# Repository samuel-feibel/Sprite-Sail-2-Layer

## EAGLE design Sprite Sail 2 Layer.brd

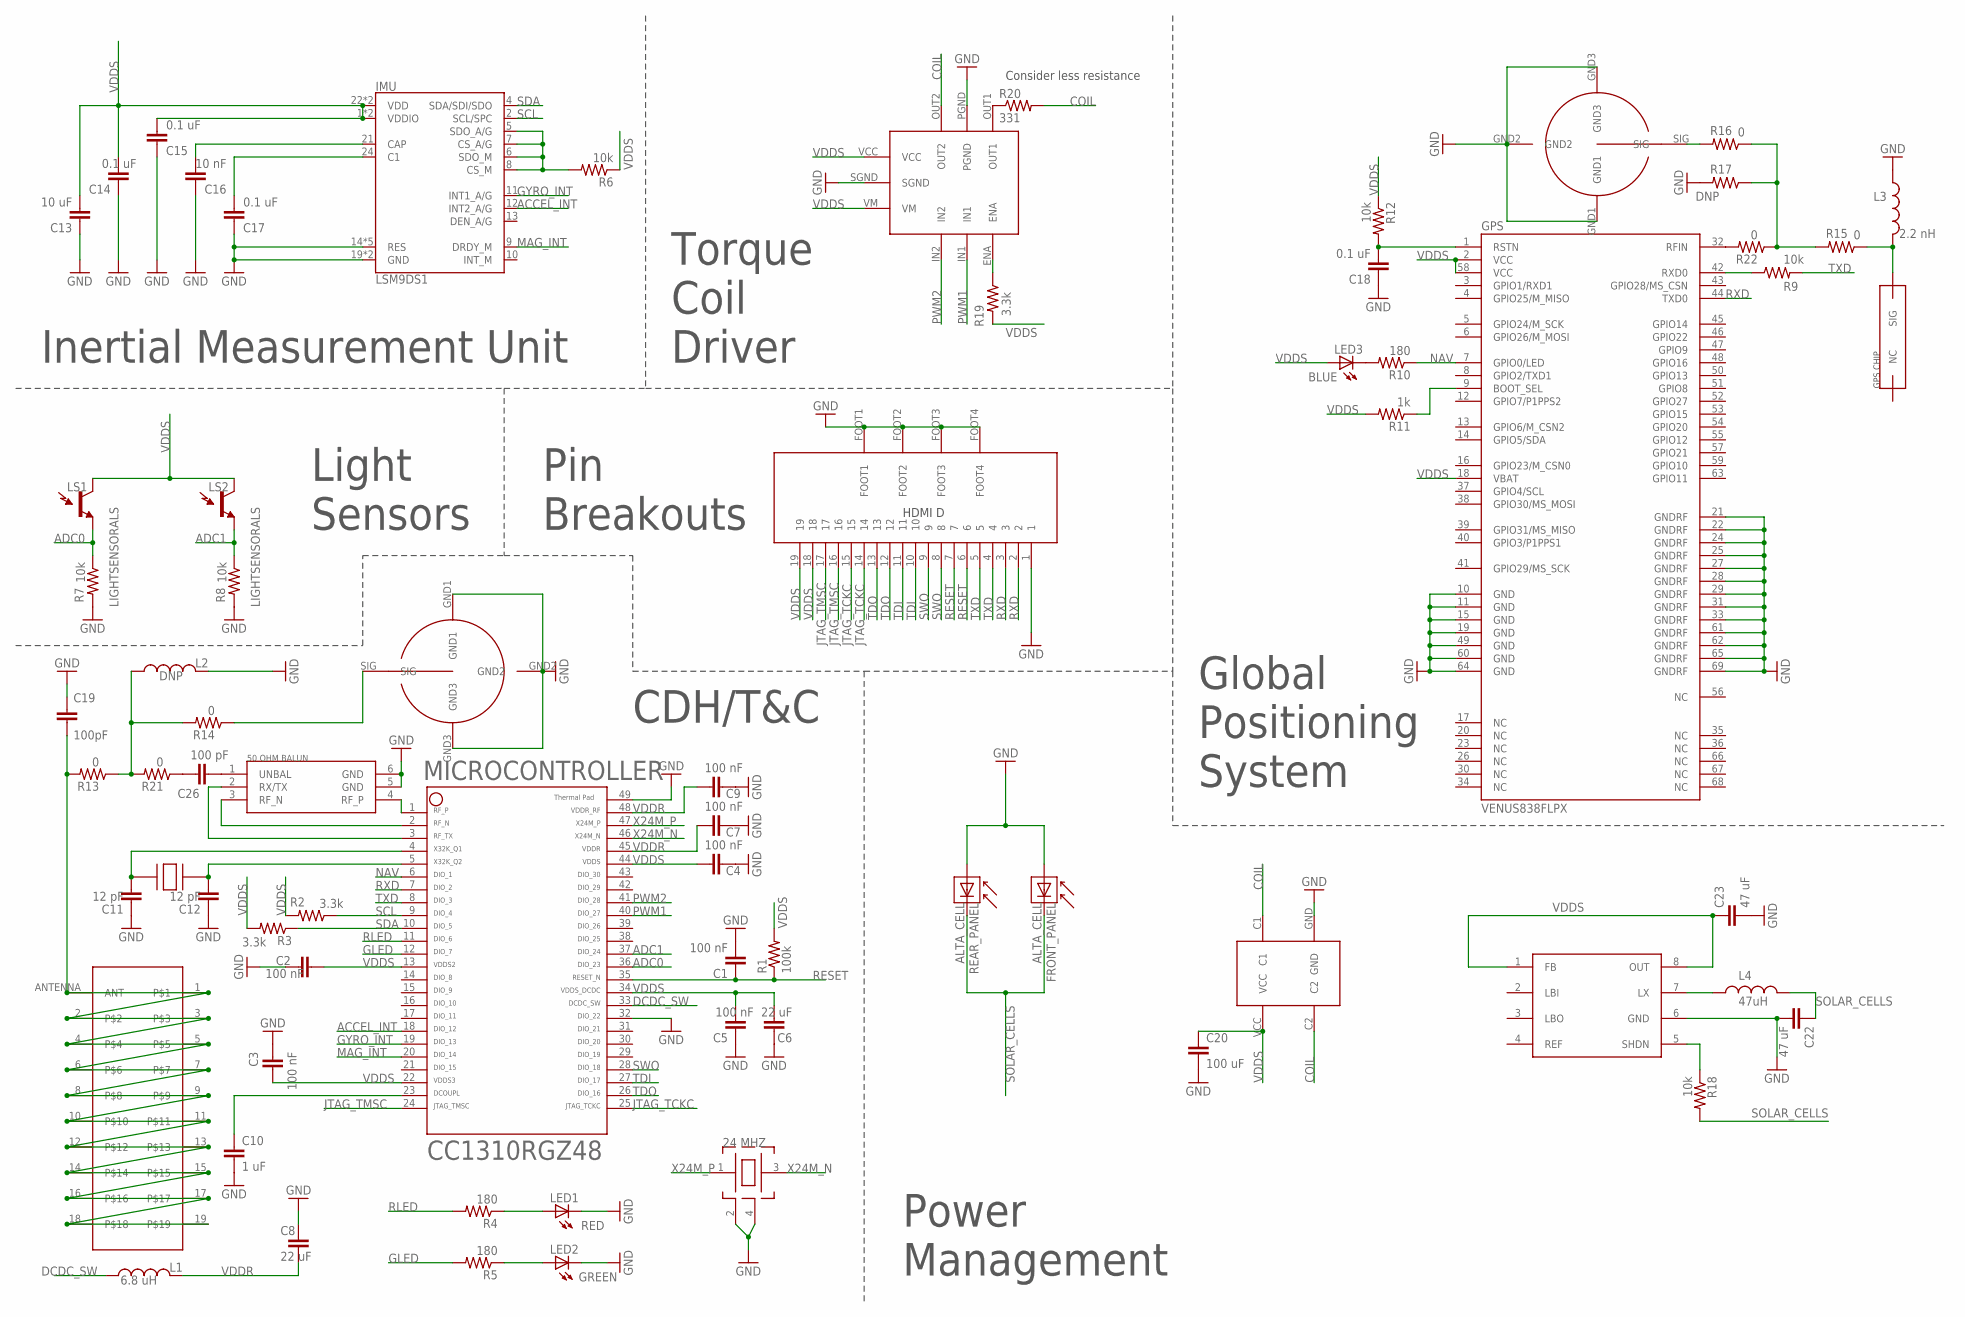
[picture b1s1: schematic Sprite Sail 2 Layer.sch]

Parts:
32.768: FC-135
BALUN: JOHANSON_BALUN
C1, C2, C3, C4, C5, C7, C9: 100 nF; 0402-CAP
C6, C8: 22 uF; 0402-CAP
C10: 1 uF; 0402-CAP
C11, C12: 12 pF; 0402-CAP
C13: 10 uF; 0402-CAP
C14, C15, C17, C18: 0.1 uF; 0402-CAP
C16: 10 nF; 0402-CAP
C19: 100pF; 0603-CAP
C20: 100 uF; 0805
C22, C23: 47 uF; 0805
C26: 100 pF; 0402-CAP
FRONT_PANEL: ALTA_CELL
GPS: VENUS838FLPX
IMU: LSM9DS1; LGA24-8X4
L1: 6.8 uH; 0603
L2: DNP; 0603
L3: 2.2 nH; 0603
L4: 47uH; 0603
LED1: RED; LED-0603
LED2: GREEN; LED-0603
LED3: BLUE; LED-0603
LS1, LS2: LIGHTSENSORALS; ALS-PT19
MICROCONTROLLER: CC1310
R1: 100k; 0402-RES
R2, R3, R19: 3.3k; 0402-RES
R4, R5, R10: 180; 0402-RES
R6, R7, R8, R9, R12, R18: 10k; 0402-RES
R11: 1k; 0402-RES
R13, R14, R15, R16, R21, R22: 0; 0603-RES
R17: DNP; 0603-RES
R20: 331; 0402-RES
REAR_PANEL: ALTA_CELL
TSX3225: TSX-3225
U$2: LV8417CS
U$3, U$7: MM5329-2700; MM5829-2700
U$4: PANASONIC_RECTIFIER
U$5: JOHANSON_GPS_CHIP
U$6: PCB_ANTENNA
U$8: L6920
U$9: HDMID

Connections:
ACCEL_INT: IMU.12 (INT2_A/G), MICROCONTROLLER.18
ADC0: LS1.E (E1), MICROCONTROLLER.36, R7.1
ADC1: LS2.E (E1), MICROCONTROLLER.37, R8.1
ANTENNA: C19.2, R13.2, U$6.1, U$6.2, U$6.3, U$6.4, U$6.5, U$6.6, U$6.7, U$6.8, U$6.9, U$6.10, U$6.11, U$6.12, U$6.13, U$6.14, U$6.15, U$6.16, U$6.17, U$6.18, U$6.19, U$6.ANTENNA (ANT)
COIL: R20.2, U$2.OUT2, U$4.C1, U$4.C2
DCDC_SW: L1.1, MICROCONTROLLER.33
GLED: MICROCONTROLLER.12, R5.2
GND: BALUN.5 (GND), BALUN.6 (GND), C1.2, C2.2, C3.2, C4.2, C5.2, C6.2, C7.2, C8.2, C9.2, C10.2, C11.2, C12.2, C13.2, C14.2, C15.2, C16.2, C17.2, C18.2, C19.1, C20.2, C22.2, C23.2, FRONT_PANEL.-, GPS.10 (GND), GPS.11 (GND), GPS.15 (GND), GPS.19 (GND), GPS.21 (GNDRF), GPS.22 (GNDRF), GPS.24 (GNDRF), GPS.25 (GNDRF), GPS.27 (GNDRF), GPS.28 (GNDRF), GPS.29 (GNDRF), GPS.31 (GNDRF), GPS.33 (GNDRF), GPS.49 (GND), GPS.60 (GND), GPS.61 (GNDRF), GPS.62 (GNDRF), GPS.64 (GND), GPS.65 (GNDRF), GPS.69 (GNDRF), IMU.14 (RES), IMU.15 (RES), IMU.16 (RES), IMU.17 (RES), IMU.18 (RES), IMU.19 (GND), IMU.20 (GND), L2.2, L3.1, LED1.C, LED2.C, MICROCONTROLLER.32, MICROCONTROLLER.49, R7.2, R8.2, R17.2, REAR_PANEL.-, TSX3225.2, TSX3225.4, U$2.PGND, U$2.SGND, U$3.GND1, U$3.GND2, U$3.GND3, U$4.GND, U$7.GND1, U$7.GND2, U$7.GND3, U$8.6 (GND), U$9.1, U$9.FOOT1, U$9.FOOT2, U$9.FOOT3, U$9.FOOT4
GYRO_INT: IMU.11 (INT1_A/G), MICROCONTROLLER.19
JTAG_TCKC: MICROCONTROLLER.25, U$9.14, U$9.15
JTAG_TMSC: MICROCONTROLLER.24, U$9.16, U$9.17
MAG_INT: IMU.9 (DRDY_M), MICROCONTROLLER.20
unnamed: C10.1, MICROCONTROLLER.23
unnamed: 32.768.P2, C11.1, MICROCONTROLLER.4
unnamed: 32.768.P1, C12.1, MICROCONTROLLER.5
unnamed: LED1.A, R4.1
unnamed: LED2.A, R5.1
unnamed: IMU.5 (SDO_A/G), IMU.6 (SDO_M), IMU.7 (CS_A/G), IMU.8 (CS_M), R6.2
unnamed: GPS.42 (RXD0), R9.1
unnamed: C16.1, IMU.21 (CAP)
unnamed: C17.1, IMU.24 (C1)
unnamed: LED3.C, R10.2
unnamed: GPS.9 (BOOT_SEL), R11.1
unnamed: C18.1, GPS.1 (RSTN), R12.2
unnamed: R15.2, R16.1, R17.1, R22.1
unnamed: L3.2, R15.1, U$5.SIG
unnamed: R16.2, U$7.SIG
unnamed: R19.1, U$2.ENA
unnamed: R20.1, U$2.OUT1
unnamed: BALUN.1 (UNBAL), C26.2
unnamed: BALUN.4 (RF_P), MICROCONTROLLER.1
unnamed: BALUN.3 (RF_N), MICROCONTROLLER.2
unnamed: BALUN.2 (RX/TX), MICROCONTROLLER.3
unnamed: GPS.32 (RFIN), R22.2
unnamed: L2.1, R13.1, R14.2, R21.2
unnamed: C26.1, R21.1
unnamed: R14.1, U$3.SIG
unnamed: R18.1, U$8.5 (SHDN)
unnamed: L4.1, U$8.7 (LX)
NAV: GPS.7 (GPIO0/LED), MICROCONTROLLER.6, R10.1
PWM1: MICROCONTROLLER.40, U$2.IN1
PWM2: MICROCONTROLLER.41, U$2.IN2
RESET: C1.1, MICROCONTROLLER.35, R1.1, U$9.6, U$9.7
RLED: MICROCONTROLLER.11, R4.2
RXD: GPS.44 (TXD0), MICROCONTROLLER.7, U$9.2, U$9.3
SCL: IMU.2 (SCL/SPC), MICROCONTROLLER.9, R2.1
SDA: IMU.4 (SDA/SDI/SDO), MICROCONTROLLER.10, R3.1
SOLAR_CELLS: C22.1, FRONT_PANEL.+, L4.2, R18.2, REAR_PANEL.+
SWO: MICROCONTROLLER.28, U$9.8, U$9.9
TDI: MICROCONTROLLER.27, U$9.10, U$9.11
TDO: MICROCONTROLLER.26, U$9.12, U$9.13
TXD: MICROCONTROLLER.8, R9.2, U$9.4, U$9.5
VDDR: C7.1, C8.1, C9.1, L1.2, MICROCONTROLLER.45, MICROCONTROLLER.48
VDDS: C2.1, C3.1, C4.1, C5.1, C6.1, C13.1, C14.1, C15.1, C20.1, C23.1, GPS.2 (VCC), GPS.18 (VBAT), GPS.58 (VCC), IMU.1 (VDDIO), IMU.3 (VDDIO), IMU.22 (VDD), IMU.23 (VDD), LED3.A, LS1.C (C1), LS2.C (C1), MICROCONTROLLER.13, MICROCONTROLLER.22, MICROCONTROLLER.34, MICROCONTROLLER.44, R1.2, R2.2, R3.2, R6.1, R11.2, R12.1, R19.2, U$2.VCC, U$2.VM, U$4.VCC, U$8.1 (FB), U$8.8 (OUT), U$9.18, U$9.19
X24M_N: MICROCONTROLLER.46, TSX3225.3
X24M_P: MICROCONTROLLER.47, TSX3225.1

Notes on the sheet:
CDH/T&C
Inertial Measurement Unit
Power Management
Light Sensors
Global Positioning System
Pin Breakouts
Torque Coil Driver
Consider less resistance

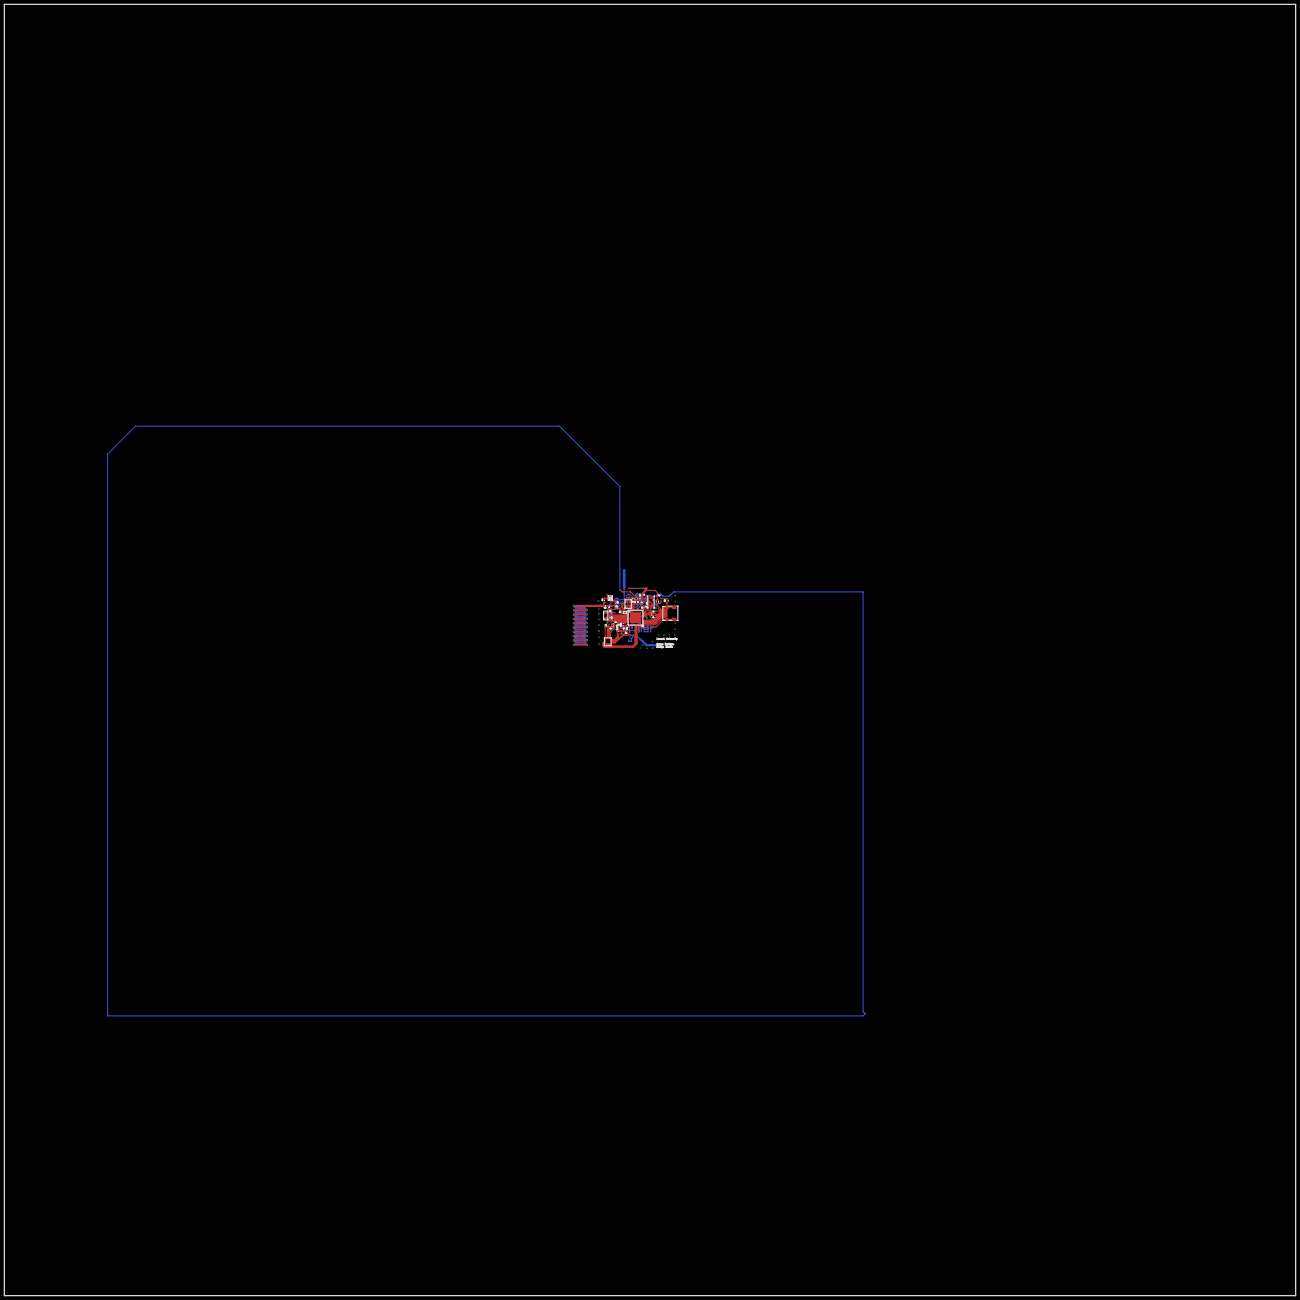
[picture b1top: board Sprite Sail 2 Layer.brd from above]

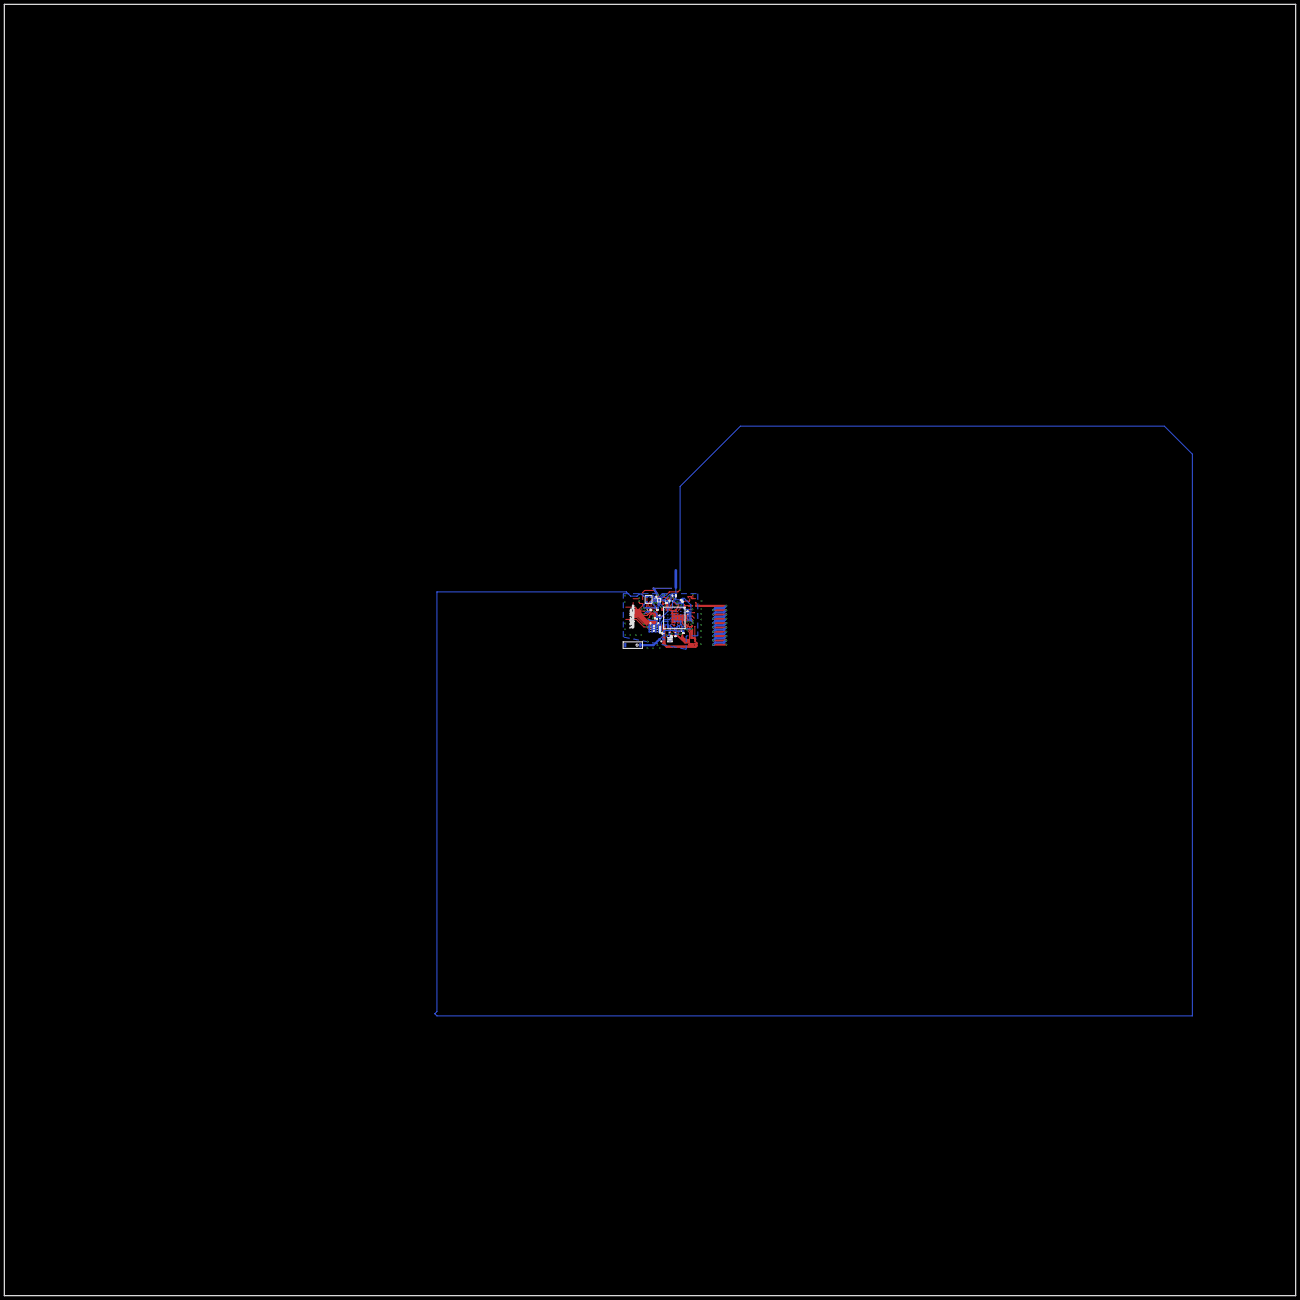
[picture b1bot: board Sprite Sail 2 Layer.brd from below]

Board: 4 copper layers, 600.0 x 600.0 mm, 68 parts (30 on the bottom side), 56 nets.

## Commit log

2018-04-30 Add files via upload
    pulled torque coils to outer layers

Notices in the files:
parts and their libraries:
SparkFun: Licensing: CC v3.0 Share-Alike You are welcome to use this library for commercial purposes.
SparkFun-Sensors: Licensing: Creative Commons ShareAlike 4.0 International - https://creativecommons.org/licenses/by-sa/4.0
